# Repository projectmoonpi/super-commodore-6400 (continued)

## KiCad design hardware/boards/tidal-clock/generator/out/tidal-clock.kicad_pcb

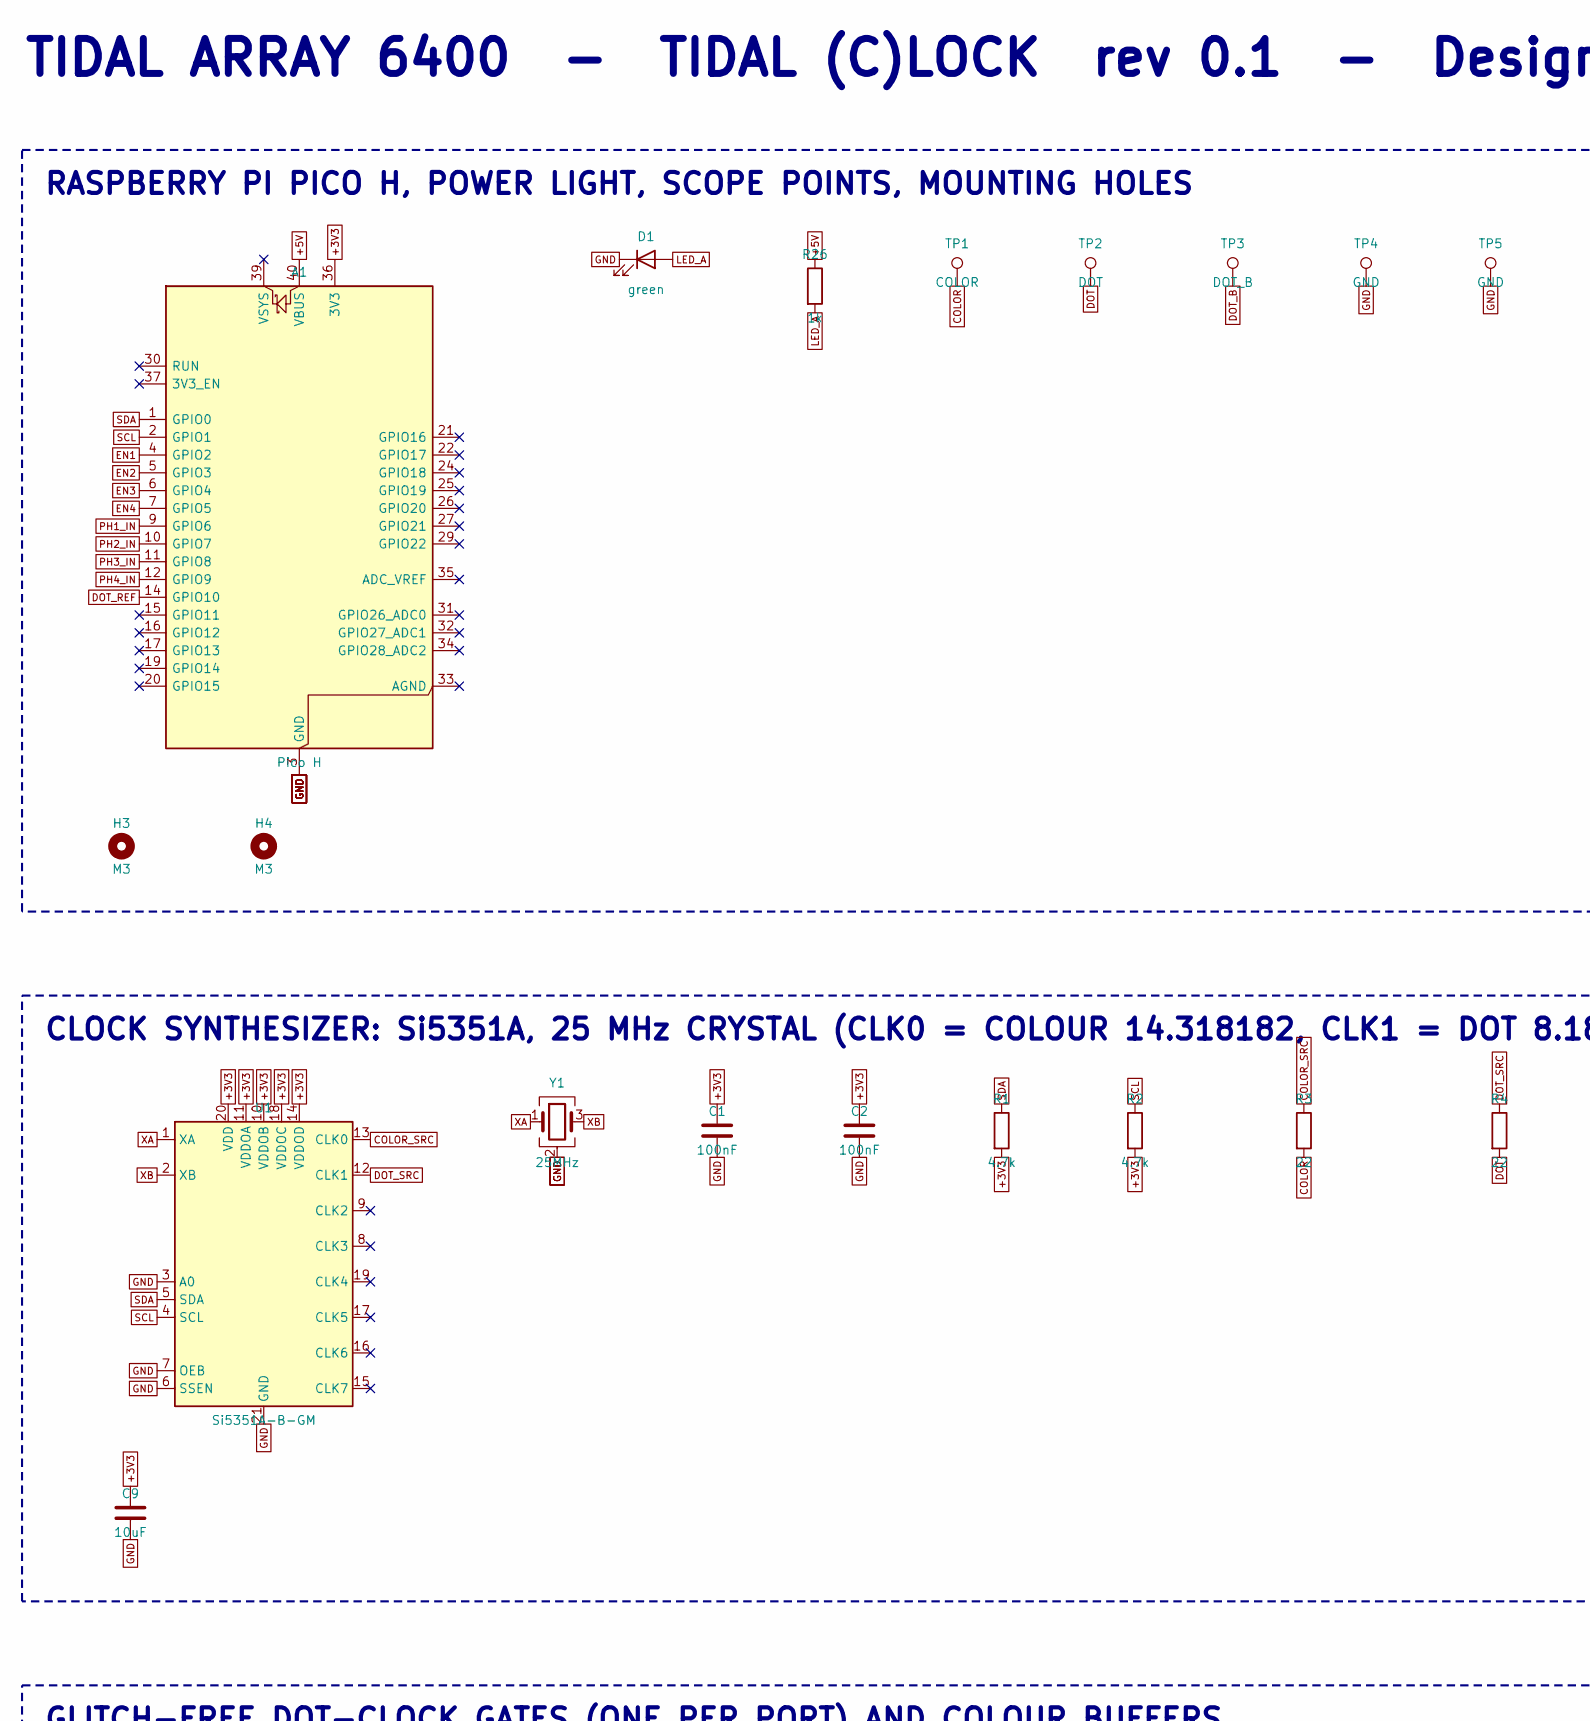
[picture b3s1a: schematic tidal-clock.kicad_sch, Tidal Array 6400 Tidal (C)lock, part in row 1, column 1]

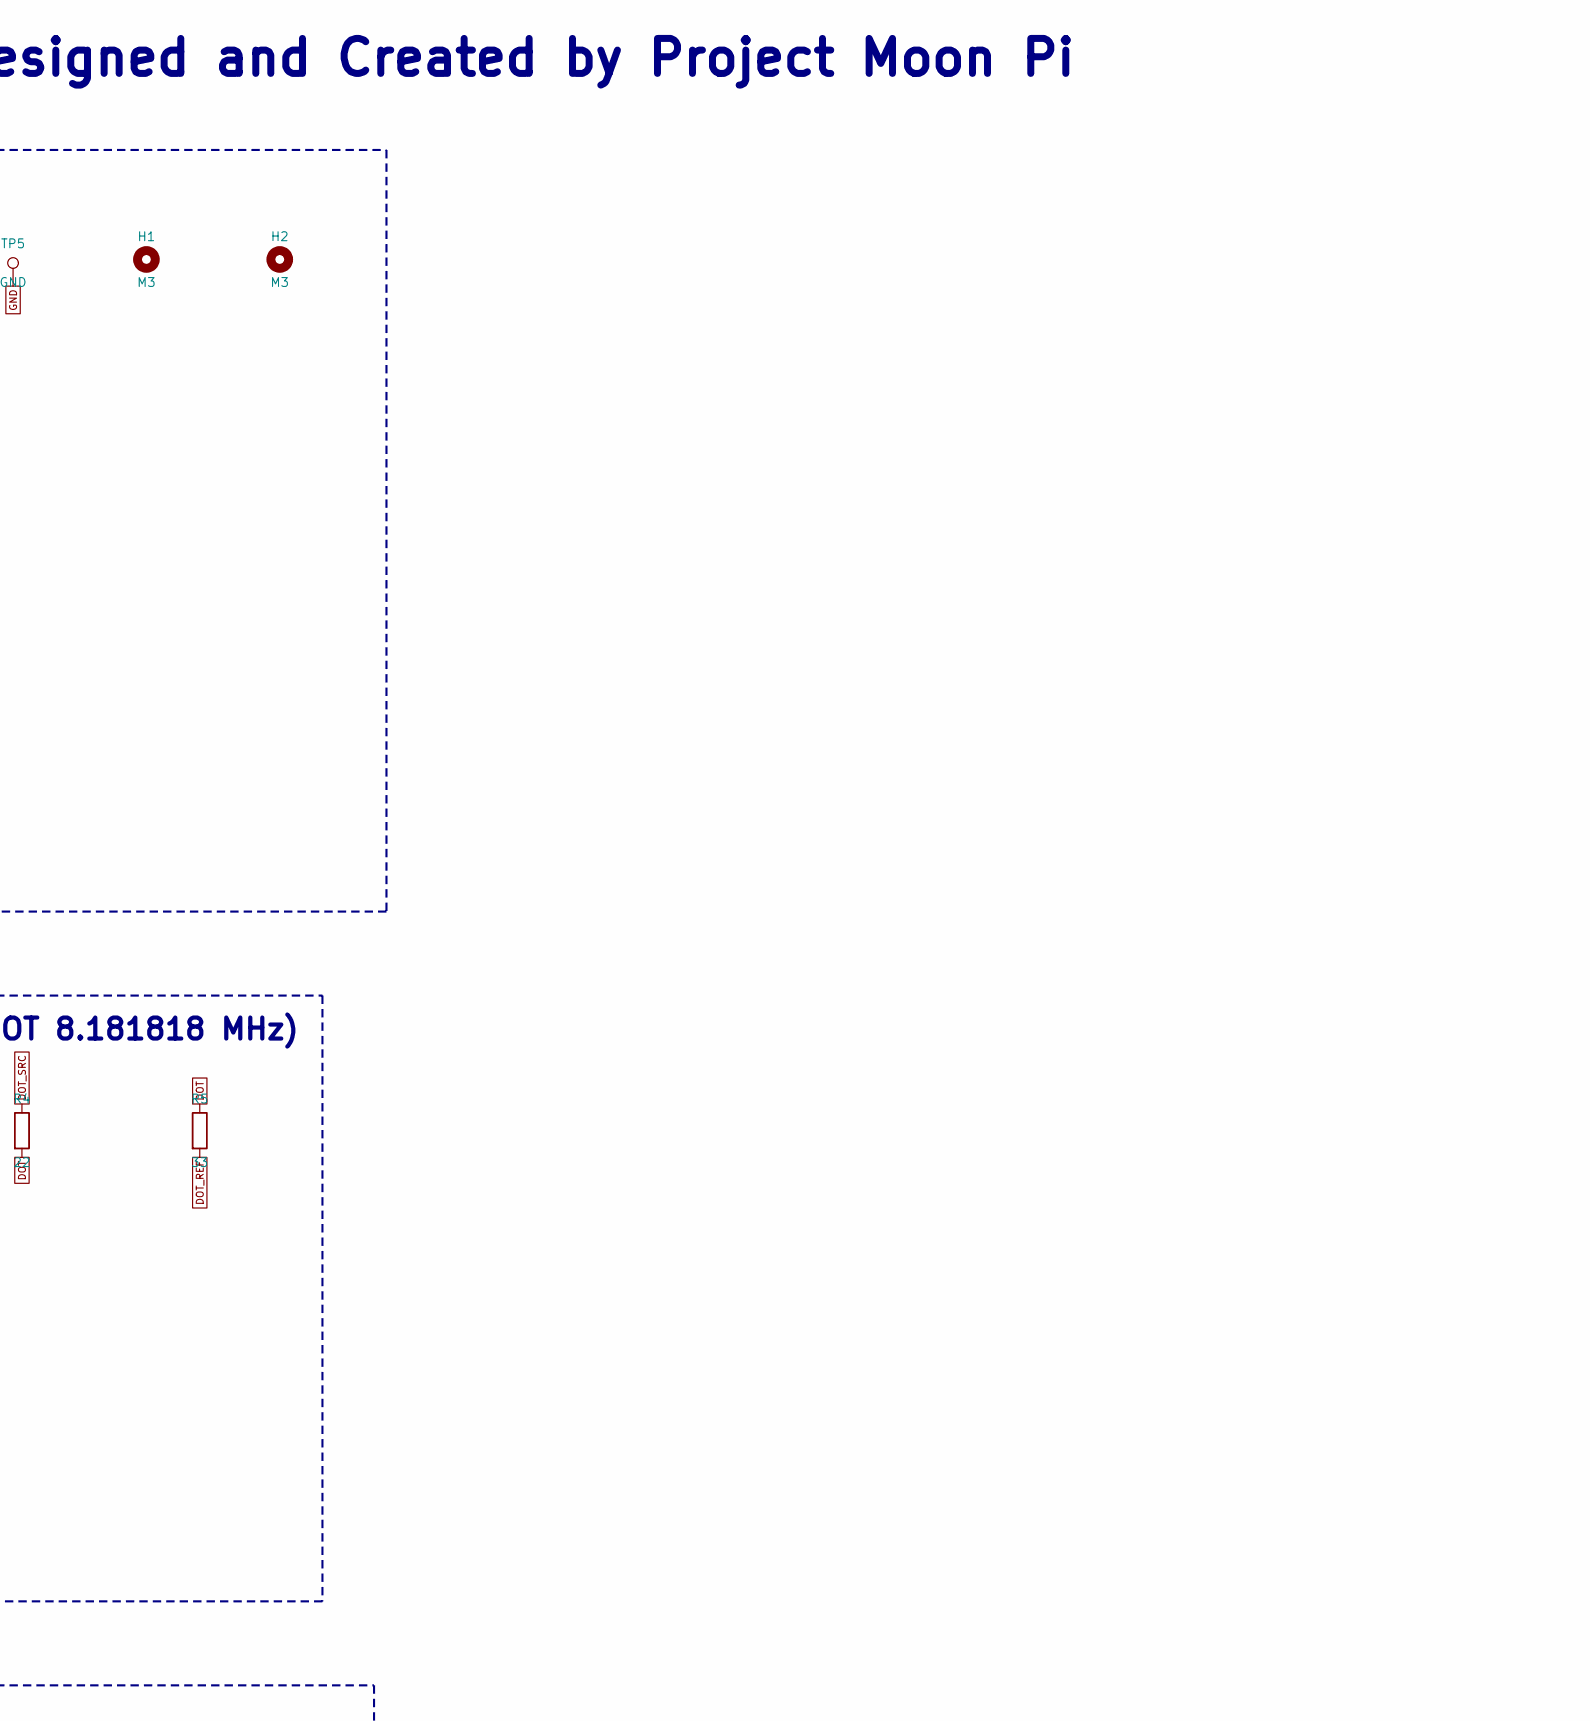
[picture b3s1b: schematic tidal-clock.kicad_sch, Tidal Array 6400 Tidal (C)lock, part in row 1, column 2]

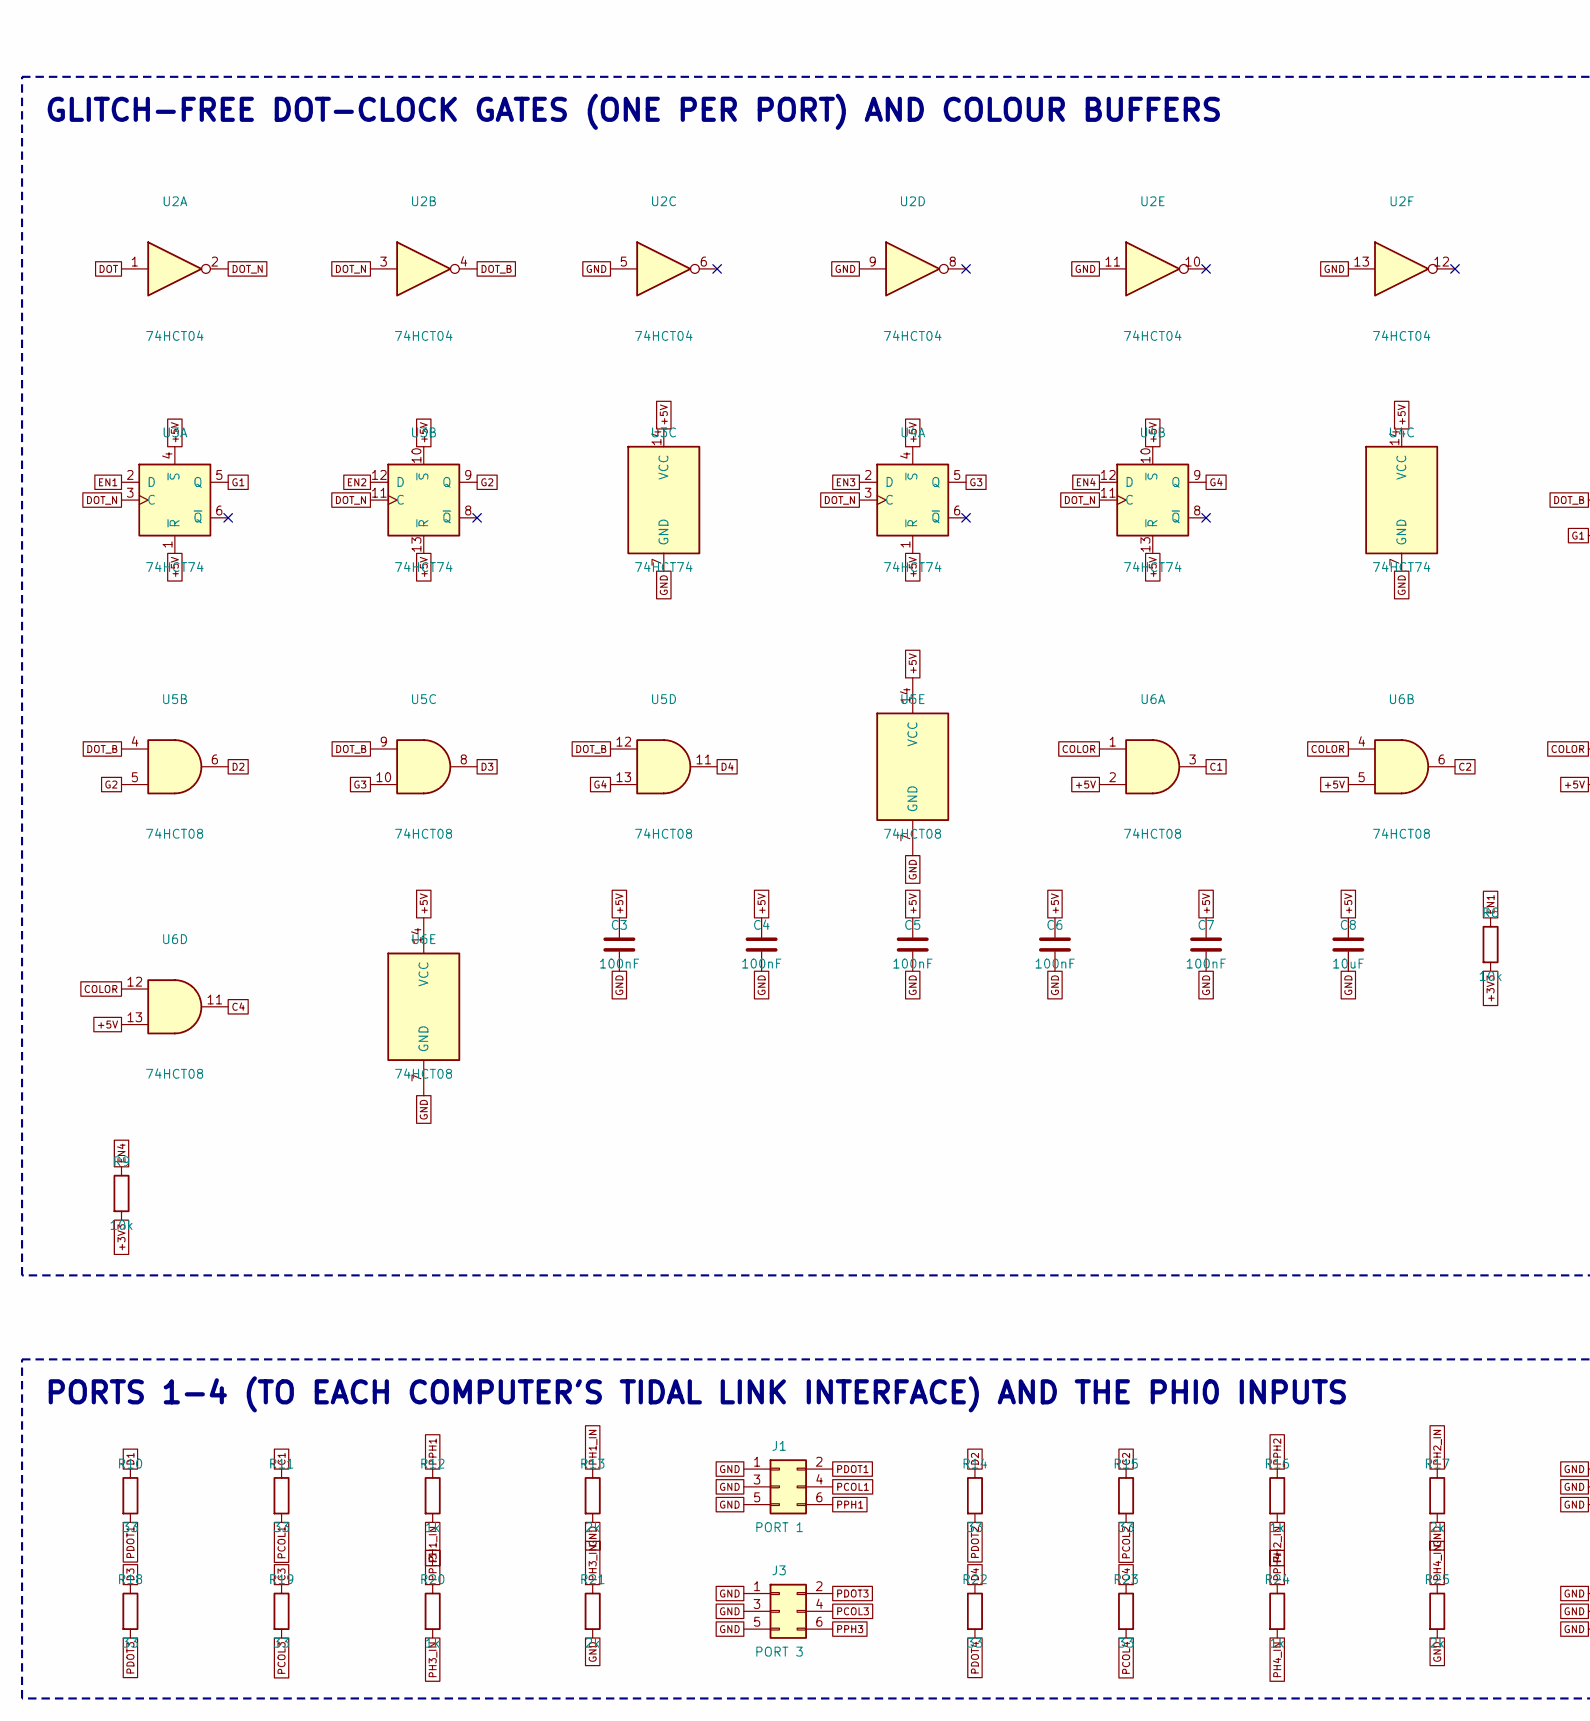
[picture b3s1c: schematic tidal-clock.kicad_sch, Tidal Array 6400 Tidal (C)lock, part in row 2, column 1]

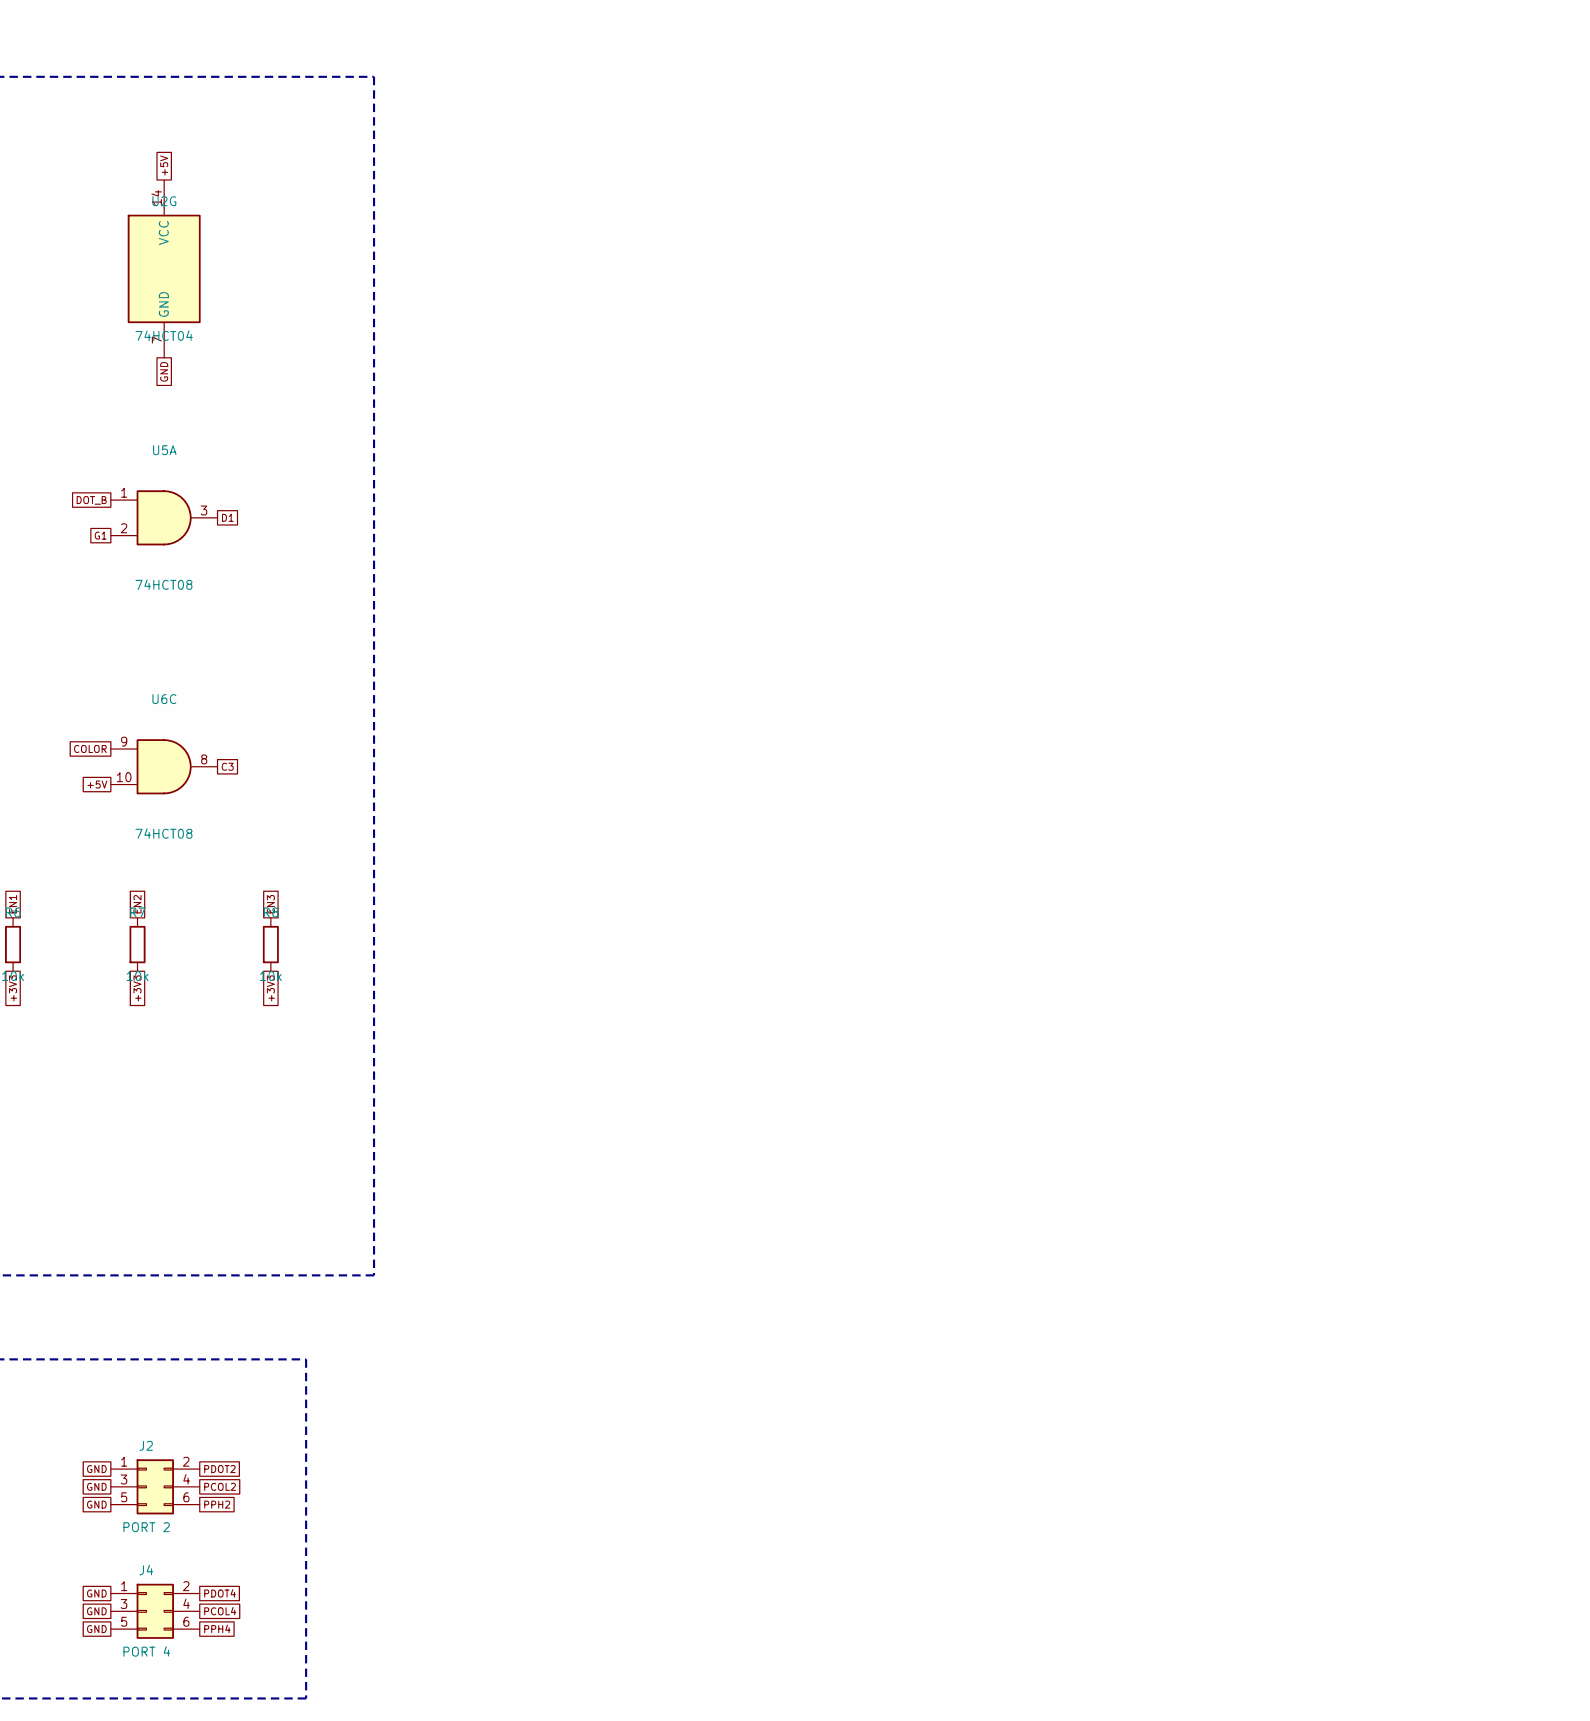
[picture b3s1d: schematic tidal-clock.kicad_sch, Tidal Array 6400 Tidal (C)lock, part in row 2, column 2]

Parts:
A1: Pico H; RaspberryPi_Pico_Common_THT; MPN SC0917
C1, C2, C3, C4, C5, C6, C7: 100nF; C_0603_1608Metric; MPN GRM188R71H104KA93D
C8, C9: 10uF; C_0805_2012Metric; MPN GRM21BR61C106KE15L
D1: green; LED_0603_1608Metric; MPN LTST-C191KGKT
H1, H2, H3, H4: M3; MountingHole_3.2mm_M3
J1: PORT 1; IDC-Header_2x03_P2.54mm_Vertical; MPN 61200621621
J2: PORT 2; IDC-Header_2x03_P2.54mm_Vertical; MPN 61200621621
J3: PORT 3; IDC-Header_2x03_P2.54mm_Vertical; MPN 61200621621
J4: PORT 4; IDC-Header_2x03_P2.54mm_Vertical; MPN 61200621621
R1, R2: 4.7k; R_0603_1608Metric; MPN RC0603FR-074K7L
R3, R4: 22; R_0603_1608Metric; MPN RC0603FR-0722RL
R5, R10, R11, R14, R15, R18, R19, R22, R23: 33; R_0603_1608Metric; MPN RC0603FR-0733RL
R6, R7, R8, R9: 10k; R_0603_1608Metric; MPN RC0603FR-0710KL
R12, R16, R20, R24, R26: 1k; R_0603_1608Metric; MPN RC0603FR-071KL
R13, R17, R21, R25: 2k; R_0603_1608Metric; MPN RC0603FR-072KL
TP1: COLOR; TestPoint_Keystone_5000-5004_Miniature; MPN 5003
TP2: DOT; TestPoint_Keystone_5000-5004_Miniature; MPN 5004
TP3: DOT_B; TestPoint_Keystone_5000-5004_Miniature; MPN 5002
TP4, TP5: GND; TestPoint_Keystone_5000-5004_Miniature; MPN 5001
U1: Si5351A-B-GM; QFN-20-1EP_4x4mm_P0.5mm_EP2.5x2.5mm; MPN SI5351A-B-GM
U2: 74HCT04; TSSOP-14_4.4x5mm_P0.65mm; MPN SN74HCT04PWR
U3, U4: 74HCT74; TSSOP-14_4.4x5mm_P0.65mm; MPN SN74HCT74PWR
U5, U6: 74HCT08; TSSOP-14_4.4x5mm_P0.65mm; MPN SN74HCT08PWR
Y1: 25MHz; Crystal_SMD_3225-4Pin_3.2x2.5mm; MPN CX3225GB25000D0HEQCC

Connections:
+3V3: A1.36 (3V3), C1.1, C2.1, C9.1, R1.2, R2.2, R6.2, R7.2, R8.2, R9.2, U1.10 (VDDOB), U1.11 (VDDOA), U1.14 (VDDOD), U1.18 (VDDOC), U1.20 (VDD)
+5V: A1.40 (VBUS), C3.1, C4.1, C5.1, C6.1, C7.1, C8.1, R26.1, U2.14 (VCC), U3.1 (~R), U3.4 (~S), U3.10 (~S), U3.13 (~R), U3.14 (VCC), U4.1 (~R), U4.4 (~S), U4.10 (~S), U4.13 (~R), U4.14 (VCC), U5.14 (VCC), U6.2, U6.5, U6.10, U6.13, U6.14 (VCC)
C1: R11.1, U6.3
C2: R15.1, U6.6
C3: R19.1, U6.8
C4: R23.1, U6.11
COLOR: R3.2, TP1.1, U6.1, U6.4, U6.9, U6.12
COLOR_SRC: R3.1, U1.13 (CLK0)
D1: R10.1, U5.3
D2: R14.1, U5.6
D3: R18.1, U5.8
D4: R22.1, U5.11
DOT: R4.2, R5.1, TP2.1, U2.1
DOT_B: TP3.1, U2.4, U5.1, U5.4, U5.9, U5.12
DOT_N: U2.2, U2.3, U3.3 (C), U3.11 (C), U4.3 (C), U4.11 (C)
DOT_REF: A1.14 (GPIO10), R5.2
DOT_SRC: R4.1, U1.12 (CLK1)
EN1: A1.4 (GPIO2), R6.1, U3.2 (D)
EN2: A1.5 (GPIO3), R7.1, U3.12 (D)
EN3: A1.6 (GPIO4), R8.1, U4.2 (D)
EN4: A1.7 (GPIO5), R9.1, U4.12 (D)
G1: U3.5 (Q), U5.2
G2: U3.9 (Q), U5.5
G3: U4.5 (Q), U5.10
G4: U4.9 (Q), U5.13
GND: A1.3 (GND), A1.8 (GND), A1.13 (GND), A1.18 (GND), A1.23 (GND), A1.28 (GND), A1.38 (GND), C1.2, C2.2, C3.2, C4.2, C5.2, C6.2, C7.2, C8.2, C9.2, D1.1 (K), J1.1, J1.3, J1.5, J2.1, J2.3, J2.5, J3.1, J3.3, J3.5, J4.1, J4.3, J4.5, R13.2, R17.2, R21.2, R25.2, TP4.1, TP5.1, U1.3 (A0), U1.6 (SSEN), U1.7 (OEB), U1.21 (GND), U2.5, U2.7 (GND), U2.9, U2.11, U2.13, U3.7 (GND), U4.7 (GND), U5.7 (GND), U6.7 (GND), Y1.2 (G), Y1.4 (G)
LED_A: D1.2 (A), R26.2
PCOL1: J1.4, R11.2
PCOL2: J2.4, R15.2
PCOL3: J3.4, R19.2
PCOL4: J4.4, R23.2
PDOT1: J1.2, R10.2
PDOT2: J2.2, R14.2
PDOT3: J3.2, R18.2
PDOT4: J4.2, R22.2
PH1_IN: A1.9 (GPIO6), R12.2, R13.1
PH2_IN: A1.10 (GPIO7), R16.2, R17.1
PH3_IN: A1.11 (GPIO8), R20.2, R21.1
PH4_IN: A1.12 (GPIO9), R24.2, R25.1
PPH1: J1.6, R12.1
PPH2: J2.6, R16.1
PPH3: J3.6, R20.1
PPH4: J4.6, R24.1
SCL: A1.2 (GPIO1), R2.1, U1.4 (SCL)
SDA: A1.1 (GPIO0), R1.1, U1.5 (SDA)
XA: U1.1 (XA), Y1.1
XB: U1.2 (XB), Y1.3

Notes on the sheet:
RASPBERRY PI PICO H, POWER LIGHT, SCOPE POINTS, MOUNTING HOLES
CLOCK SYNTHESIZER: Si5351A, 25 MHz CRYSTAL (CLK0 = COLOUR 14.318182, CLK1 = DOT 8.181818 MHz)
GLITCH-FREE DOT-CLOCK GATES (ONE PER PORT) AND COLOUR BUFFERS
PORTS 1-4 (TO EACH COMPUTER'S TIDAL LINK INTERFACE) AND THE PHI0 INPUTS
TIDAL ARRAY 6400 - TIDAL (C)LOCK rev 0.1 - Designed and Created by Project Moon Pi

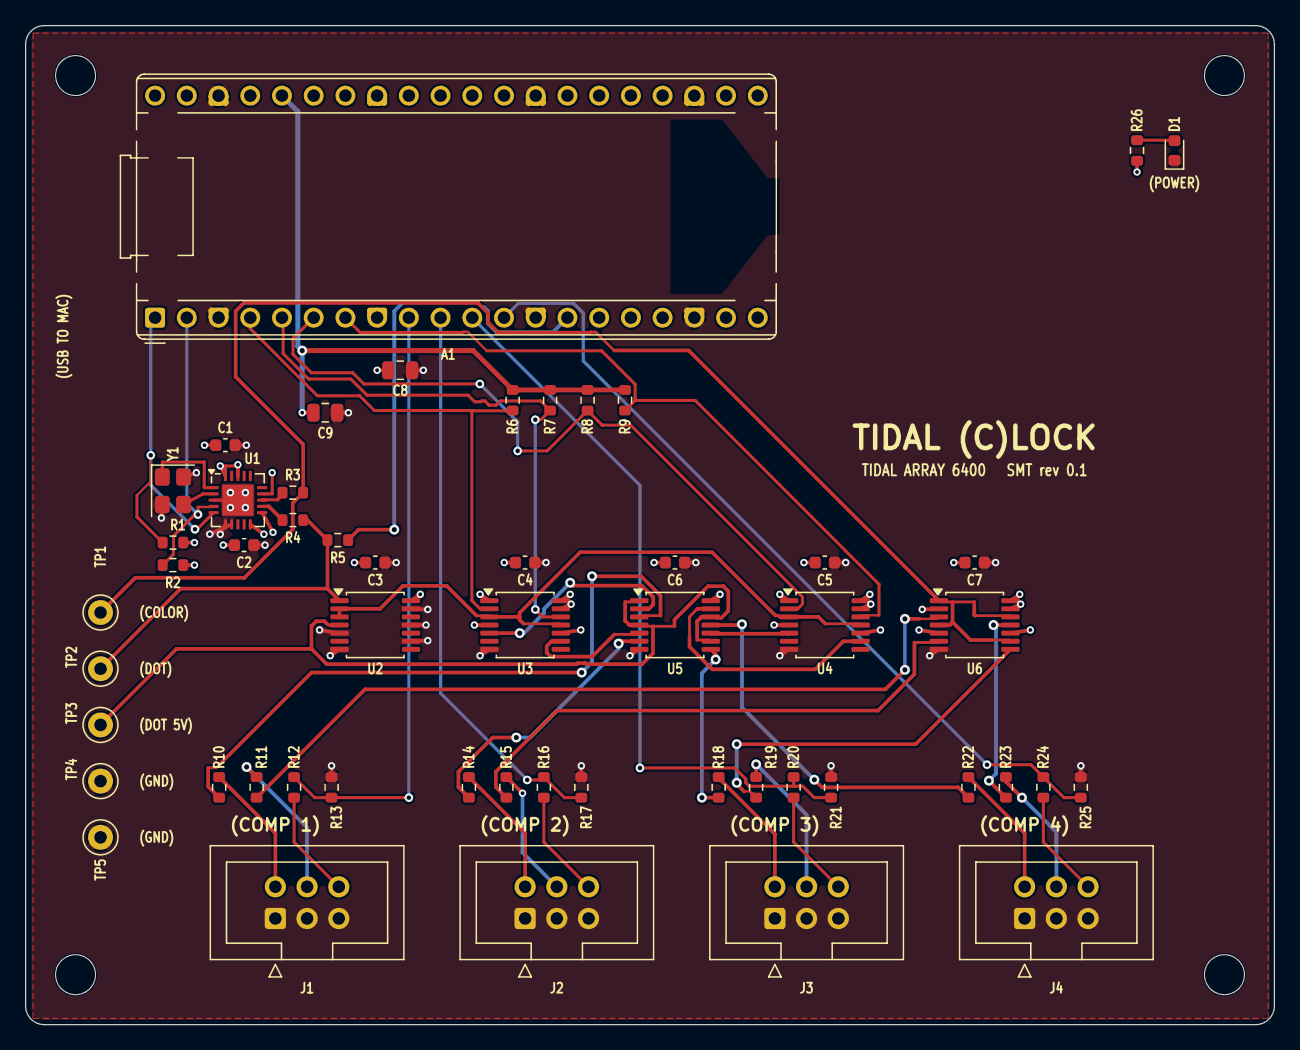
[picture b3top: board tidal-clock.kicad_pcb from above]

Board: 4 copper layers, 100.0 x 80.0 mm, 57 parts (0 on the bottom side), 47 nets.

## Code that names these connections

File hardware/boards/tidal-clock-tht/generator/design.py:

"""Tidal Array 6400 - Tidal (C)lock, THROUGH-HOLE EDITION, rev 0.1: one master clock for up to 4 C64s.

The same circuit as the SMT edition (hardware/boards/tidal-clock), built from parts you can solder by hand and buy
today, so the bench test can start before any assembled board arrives:

    Adafruit Si5351A board (#2045)  the clock synthesizer, ready made (its own 25 MHz crystal and 3.3 V regulator),
                                    plugged into a 7-way socket. CLK0 = 14.318182 MHz colour, CLK1 = 8.181818 MHz
                                    dot, exactly as on the SMT edition. Powered from the Pico's 3.3 V, so its I2C
                                    pull-ups stay at 3.3 V (the Pico's pins are not 5 V tolerant).
    74HCT04 / 74HCT74 / 74HCT08     the glitch-free gates and colour buffers, in DIP-14 (socketed).
    Raspberry Pi Pico H             on two 20-way sockets, as on the SMT edition.
    GP11 (Pico pin 15) tied to GND  tells the firmware this is the through-hole edition (the Adafruit board's
                                    crystal wants a 10 pF load setting; the SMT edition's wants 8 pF).

Same ports (6-way box headers, wired as the Tidal Link Interface's J3: 1 GND, 2 DOT, 3 GND, 4 COLOR, 5 GND,
6 PHI0 in), same firmware. Run build.sh after changing anything here. Designed and Created by Project Moon Pi.
"""

FP_R = "Resistor_THT:R_Axial_DIN0207_L6.3mm_D2.5mm_P10.16mm_Horizontal"
FP_C = "Capacitor_THT:C_Rect_L4.0mm_W2.5mm_P2.50mm"
FP_CP = "Capacitor_THT:CP_Radial_D5.0mm_P2.00mm"
FP_DIP = "Package_DIP:DIP-14_W7.62mm_Socket"
FP_PICO = "Module:RaspberryPi_Pico_Common_THT"
FP_SYNTH = "Connector_PinSocket_2.54mm:PinSocket_1x07_P2.54mm_Vertical"
FP_IDC = "Connector_IDC:IDC-Header_2x03_P2.54mm_Vertical"
FP_TP = "TestPoint:TestPoint_Keystone_5000-5004_Miniature"
FP_LED = "LED_THT:LED_D3.0mm"
FP_HOLE = "MountingHole:MountingHole_3.2mm_M3"
NPORTS = 4

PARTS = []


def part(ref, lib, value, fp, pins, group, desc="", mfr="", mpn=""):
    PARTS.append(dict(ref=ref, lib=lib, value=value, fp=fp, pins={str(k): v for k, v in pins.items()}, group=group,
                      desc=desc, mfr=mfr, mpn=mpn))


_n = {"R": 0, "C": 0}


def nxt(k):
    _n[k] += 1
    return f"{k}{_n[k]}"


RES = {"22": "MFR-25FBF52-22R", "33": "MFR-25FBF52-33R", "1k": "MFR-25FBF52-1K", "2k": "MFR-25FBF52-2K",
       "10k": "MFR-25FBF52-10K"}


def R(val, a, b, grp, desc=""):
    r = nxt("R")
    part(r, "Device:R", val, FP_R, {1: a, 2: b}, grp, desc + " (1/4 W metal film)", "Yageo", RES[val])
    return r


def C(val, a, b, grp, desc=""):
    r = nxt("C")
    if val == "10uF":
        part(r, "Device:C_Polarized", val, FP_CP, {1: a, 2: b}, grp, desc + " (25 V electrolytic: + to the long lead)",
             "KEMET", "ESK106M025AC3AA")
    else:
        part(r, "Device:C", val, FP_C, {1: a, 2: b}, grp, desc, "TDK", "FG18X7R1H104KNT06")
    return r


# ---------------------------------------------------------------- the Pico H (on two 20-way sockets)
pico = {3: "GND", 8: "GND", 13: "GND", 18: "GND", 23: "GND", 28: "GND", 38: "GND",   # (33, AGND: joined to GND inside the Pico)
        36: "+3V3", 40: "+5V",
        1: "SDA", 2: "SCL",                                        # I2C0 to the Si5351 board
        4: "EN1", 5: "EN2", 6: "EN3", 7: "EN4",                    # GP2-GP5: the dot-clock gates
        9: "PH1_IN", 10: "PH2_IN", 11: "PH3_IN", 12: "PH4_IN",     # GP6-GP9: each machine's PHI0 (PIO reads 4 at once)
        14: "DOT_REF",                                             # GP10: the ungated dot clock, for PIO timing
        15: "EDITION"}                                             # GP11 held low (R below): "through-hole edition"
part("A1", "MCU_Module:RaspberryPi_Pico", "Pico H", FP_PICO, pico, "pico",
     "Raspberry Pi Pico H (headers fitted), plugged into two 20-way sockets (Sullins PPTC201LFBN-RC x2)",
     "Raspberry Pi", "SC0917")

# ---------------------------------------------------------------- the clock synthesizer: Adafruit's board
part("M1", "Connector_Generic:Conn_01x07", "Adafruit 2045", FP_SYNTH,
     {1: "COLOR_SRC", 2: "DOT_SRC", 4: "SCL", 5: "SDA", 6: "GND", 7: "+3V3"}, "synth",
     "Adafruit Si5351A clock generator board (#2045), its 7-pin header in a 7-way socket (Sullins PPTC071LFBN-RC): "
     "CLK0, CLK1, CLK2 (unused), SCL, SDA, GND, VIN", "Adafruit", "2045")
C("100nF", "+3V3", "GND", "synth", "Si5351 board supply")
C("10uF", "+3V3", "GND", "synth", "3.3 V bulk")
R("22", "COLOR_SRC", "COLOR", "synth", "series termination")
R("22", "DOT_SRC", "DOT", "synth", "series termination")
R("33", "DOT", "DOT_REF", "synth", "to the Pico")

# ---------------------------------------------------------------- the gates (as the SMT edition, in DIP-14)
part("U2", "74xx:74HCT04", "74HCT04", FP_DIP,
     {1: "DOT", 2: "DOT_N", 3: "DOT_N", 4: "DOT_B", 5: "GND", 9: "GND", 11: "GND", 13: "GND", 7: "GND", 14: "+5V"},
     "gates", "DOT_N (flip-flops' clock: they change on the dot clock's falling edge), DOT_B (5 V dot clock). "
     "In a 14-pin socket (On Shore ED14DT)", "Texas Instruments", "SN74HCT04N")
for u, (a, b) in (("U3", (1, 2)), ("U4", (3, 4))):
    part(u, "74xx:74HCT74", "74HCT74", FP_DIP,
         {1: "+5V", 2: f"EN{a}", 3: "DOT_N", 4: "+5V", 5: f"G{a}",
          13: "+5V", 12: f"EN{b}", 11: "DOT_N", 10: "+5V", 9: f"G{b}", 7: "GND", 14: "+5V"},
         "gates", f"gate flip-flops, ports {a} and {b}. In a 14-pin socket (On Shore ED14DT)", "Texas Instruments",
         "SN74HCT74N")
part("U5", "74xx:74LS08", "74HCT08", FP_DIP,
     {1: "DOT_B", 2: "G1", 3: "D1", 4: "DOT_B", 5: "G2", 6: "D2", 9: "DOT_B", 10: "G3", 8: "D3",
      12: "DOT_B", 13: "G4", 11: "D4", 7: "GND", 14: "+5V"},
     "gates", "the gated dot clocks. In a 14-pin socket (On Shore ED14DT)", "Texas Instruments", "SN74HCT08N")
part("U6", "74xx:74LS08", "74HCT08", FP_DIP,
     {1: "COLOR", 2: "+5V", 3: "C1", 4: "COLOR", 5: "+5V", 6: "C2", 9: "COLOR", 10: "+5V", 8: "C3",
      12: "COLOR", 13: "+5V", 11: "C4", 7: "GND", 14: "+5V"},
     "gates", "colour clock buffers (an AND with one input high), never gated. In a 14-pin socket (On Shore ED14DT)",
     "Texas Instruments", "SN74HCT08N")
for u in ("U2", "U3", "U4", "U5", "U6"):
    C("100nF", "+5V", "GND", "gates", f"{u} decoupling")
C("10uF", "+5V", "GND", "gates", "5 V bulk")
for k in range(1, NPORTS + 1):
    R("10k", f"EN{k}", "+3V3", "gates", f"gate {k} open until the Pico says otherwise")

# ---------------------------------------------------------------- the ports
for k in range(1, NPORTS + 1):
    R("33", f"D{k}", f"PDOT{k}", "ports", f"port {k} dot clock out")
    R("33", f"C{k}", f"PCOL{k}", "ports", f"port {k} colour clock out")
    # each C64's 5 V PHI0 to the Pico's 3.3 V input: a 1k / 2k divider (3.33 V), which also holds an empty port low
    R("1k", f"PPH{k}", f"PH{k}_IN", "ports", f"port {k} PHI0 in")
    R("2k", f"PH{k}_IN", "GND", "ports", f"port {k}: no cable reads low")
    part(f"J{k}", "Connector_Generic:Conn_02x03_Odd_Even", f"PORT {k}", FP_IDC,
         {1: "GND", 2: f"PDOT{k}", 3: "GND", 4: f"PCOL{k}", 5: "GND", 6: f"PPH{k}"}, "ports",
         f"to computer {k}'s Tidal Link Interface (J3)", "Wurth Elektronik", "61200621621")

# ---------------------------------------------------------------- power light, scope points, mounting holes
part("D1", "Device:LED", "green", FP_LED, {1: "GND", 2: "LED_A"}, "pico", "power light, 3 mm green (long lead = +)",
     "Lite-On", "LTL-4231N")
R("1k", "+5V", "LED_A", "pico", "power light")
R("1k", "EDITION", "GND", "pico", "edition strap: GP11 low tells the firmware this is the through-hole board")
for ref, net, colour, mpn in (("TP1", "COLOR", "orange", "5003"), ("TP2", "DOT", "yellow", "5004"),
                              ("TP3", "DOT_B", "white", "5002"), ("TP4", "GND", "black", "5001"),
                              ("TP5", "GND", "black", "5001")):
    part(ref, "Connector:TestPoint", net, FP_TP, {1: net}, "pico", f"scope test point ({colour})", "Keystone", mpn)
for i in range(1, 5):
    part(f"H{i}", "Mechanical:MountingHole", "M3", FP_HOLE, {}, "pico", "M3 mounting hole")

NETCLASSES = {"Power": (0.6, 0.2, ["+5V", "GND"]),
              "Power33": (0.4, 0.2, ["+3V3"]),
              "Clock": (0.3, 0.2, ["COLOR*", "DOT*", "D?", "C?", "PDOT*", "PCOL*", "G?"])}
DEFAULT_TRACK, DEFAULT_CLEAR = 0.25, 0.2
